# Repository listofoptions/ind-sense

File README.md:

# ind-sense
a prototype mechanical keyboard design based on inductive and capacitive sensing

project folder layout:
* cad        - contains the kicad and autocad files for pcb and switch design
* datasheets - information about the mechanical and electrical components used
* jupyter    - ipython notebook for the theory of operation 
* layout     - proposed eventual keyboard layouts
* scripts    - help scripts for use with design
* spice      - ltspice simulation source 

the main driving idea behind this keyboard switch design is to to build an even
more reliable beam spring like keyboard, that is a non conductivly sensed switch
with a high lifetime. the main mechanism of failure of most capacitive switches
is dirt and dust sensitivity, 
# ind-sense
a prototype mechanical keyboard design based on inductive and capacitive sensing

project folder layout:
* cad        - contains the kicad and autocad files for pcb and switch design
* datasheets - information about the mechanical and electrical components used
* jupyter    - ipython notebook for the theory of operation 
* layout     - proposed eventual keyboard layouts
* scripts    - help scripts for use with design
* spice      - ltspice simulation source 

the main driving idea behind this keyboard switch design is to to build an even
more reliable beam spring like keyboard, that is a non conductivly sensed switch
with a high lifetime. the main mechanism of failure of most capacitive switches
is dirt and dust sensitivity, which can be mitigated against by the use of a
spacer. This however makes the capacitive mechanism useless, (too much distance
at low voltages) to ensure the functionality of a such a mechanism I use an
inductive pad as the sensing element, such that when a peice of silicon steel
laminate is placed near the pad (with a protective spacer between!) the 
inductance, and hence the impedence of the circuit is changed. this of couse can
be sensed by the controller.

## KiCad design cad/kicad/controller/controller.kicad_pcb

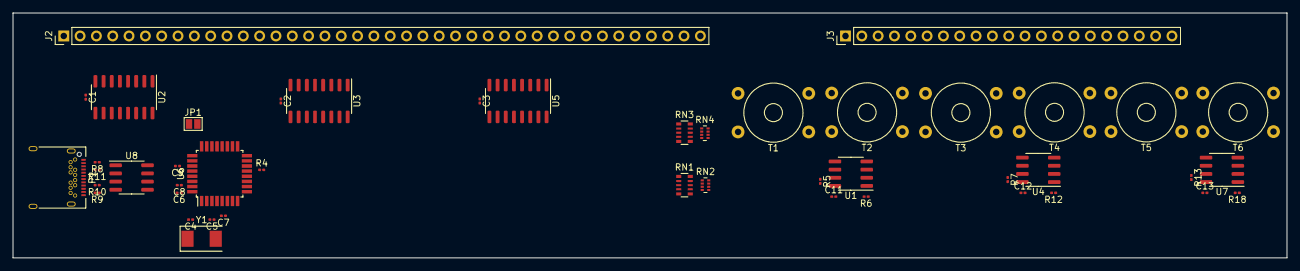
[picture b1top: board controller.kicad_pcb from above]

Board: 2 copper layers, 198.2 x 38.1 mm, 46 parts (0 on the bottom side), 86 nets, no tracks yet.

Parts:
C1, C2, C3, C6, C7, C8, C11, C12, C13: 0U1; C_0201_0603Metric
C4, C5: 22P; C_0201_0603Metric
C9: 1U; C_0201_0603Metric
J2: COLUMNS; PinHeader_1x40_P2.54mm_Vertical
J3: ROW; PinHeader_1x21_P2.54mm_Vertical
JP1: RESET; SolderJumper-2_P1.3mm_Open_Pad1.0x1.5mm
P1: USB_C_Plug_USB2.0; USB_C_Receptacle_Amphenol_12401548E4-2A
R4, R5, R6, R7, R12, R13, R18: 10K; R_0201_0603Metric
R8, R9: 5K1; R_0201_0603Metric
R10, R11: 22; R_0201_0603Metric
RN1, RN3: R_Pack05; R_Array_Convex_5x0603
RN2, RN4: R_Pack04; R_Array_Concave_4x0402
T1, T2, T3, T4, T5, T6: Transformer_1P_1S; Transformer_Toroid_Horizontal_D9.0mm_Amidon-T30
U1, U4, U7: LM393; SOIC-8_3.9x4.9mm_P1.27mm
U2, U3, U5: 74HC595; SOIC-16_3.9x9.9mm_P1.27mm
U6: ATmega32U2-AU; TQFP-32_7x7mm_P0.8mm
U8: USB6B1; SOIC-8_3.9x4.9mm_P1.27mm
Y1: 16M; Crystal_SMD_0603-2Pin_6.0x3.5mm

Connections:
+5V: C1.1, C2.1, C3.1, C6.1, C7.1, C8.1, C11.1, C12.1, C13.1, P1.A4, P1.A9, P1.B4, P1.B9, R5.2, R6.2, R7.2, R12.2, R13.2, R18.2, U1.8, U2.16, U3.16, U4.8, U5.16, U6.4, U6.31, U6.32, U7.8, U8.1, U8.8
/CLOCK: U2.11, U3.11, U5.11, U6.15
/COL1: J2.3, U2.7
/COL2: J2.5, U2.6
/COL3: J2.6, U2.5
/COL4: J2.8, U2.4
/COL5: J2.9, U2.3
/COL6: J2.11, U2.2
/COL7: J2.12, U2.1
/COL8: J2.14, U2.15
/COL9: J2.15, U3.7
/COL10: J2.17, U3.6
/COL11: J2.18, U3.5
/COL12: J2.20, U3.4
/COL13: J2.21, U3.3
/COL14: J2.23, U3.2
/COL15: J2.24, U3.1
/COL16: J2.26, U3.15
/COL17: J2.27, U5.7
/COL18: J2.29, U5.6
/COL19: J2.30, U5.5
/COL20: J2.32, U5.4
/COL21: J2.33, U5.3
/COL22: J2.35, U5.2
/COL23: J2.36, U5.1
/COL24: J2.38, U5.15
/CROWREF: RN1.10, RN2.8, U1.2, U1.6, U4.2, U4.6, U7.2, U7.6
/CROWREFDAC1: RN1.1, U6.26
/CROWREFDAC2: RN1.2, U6.25
/CROWREFDAC3: RN1.3, U6.23
/CROWREFDAC4: RN1.4, U6.22
/D+: U6.29, U8.7
/D-: U6.30, U8.6
/LE: U2.12, U3.12, U5.12, U6.18
/OUT1: R18.1, U6.11, U7.1
/OUT2: R13.1, U6.10, U7.7
/OUT3: R12.1, U4.1, U6.9
/OUT4: R7.1, U4.7, U6.8
/OUT5: R6.1, U1.1, U6.7
/OUT6: R5.1, U1.7, U6.6
/ROW1: T1.3, U1.5
/ROW1+: J3.3, T1.2
/ROW1-: J3.4, T1.1
/ROW2: T2.3, U1.3
/ROW2+: J3.6, T2.2
/ROW2-: J3.7, T2.1
/ROW3: T3.3, U4.5
/ROW3+: J3.9, T3.2
/ROW3-: J3.10, T3.1
/ROW4: T4.3, U4.3
/ROW4+: J3.12, T4.2
/ROW4-: J3.13, T4.1
/ROW5: T5.3, U7.5
/ROW5+: J3.15, T5.2
/ROW5-: J3.16, T5.1
/ROW6: T6.3, U7.3
/ROW6+: J3.18, T6.2
/ROW6-: J3.19, T6.1
/SDI: U2.14, U6.16
/STAGE1: U2.9, U3.14
/STAGE2: U3.9, U5.14
/TROWREF: RN3.10, RN4.8, T1.4, T2.4, T3.4, T4.4, T5.4, T6.4
/TROWREFDAC1: RN3.1, U6.19
/TROWREFDAC2: RN3.2, U6.20
/TROWREFDAC3: RN3.3, U6.21
/TROWREFDAC4: RN3.4, U6.5
/X+: C5.1, U6.2, Y1.2
/X-: C4.2, U6.1, Y1.1
/~OE: U2.13, U3.13, U5.13, U6.14
GND: C1.2, C2.2, C3.2, C4.1, C5.2, C6.2, C7.2, C8.2, C9.2, C11.2, C12.2, C13.2, JP1.1, P1.A1, P1.A12, P1.B1, P1.B12, P1.S1, R4.2, R8.1, R9.1, U1.4, U2.8, U2.10, U3.8, U3.10, U4.4, U5.8, U5.10, U6.3, U6.28, U7.4, U8.4, U8.5
GNDREF: J2.1, J2.2, J2.4, J2.7, J2.10, J2.13, J2.16, J2.19, J2.22, J2.25, J2.28, J2.31, J2.34, J2.37, J2.39, J2.40, J3.1, J3.2, J3.5, J3.8, J3.11, J3.14, J3.17, J3.20, J3.21, RN1.5, RN3.5
unnamed: C9.1, U6.27
unnamed: JP1.2, U6.24
unnamed: P1.A5, R8.2
unnamed: P1.A6, R11.2
unnamed: P1.A7, R10.2
unnamed: P1.B5, R9.2
unnamed: R4.1, U6.13
unnamed: R10.1, U8.3
unnamed: R11.1, U8.2
unnamed: RN1.6, RN1.7, RN2.3
unnamed: RN1.8, RN2.6, RN2.7
unnamed: RN1.9, RN2.1
unnamed: RN3.6, RN3.7, RN4.3
unnamed: RN3.8, RN4.6, RN4.7
unnamed: RN3.9, RN4.1

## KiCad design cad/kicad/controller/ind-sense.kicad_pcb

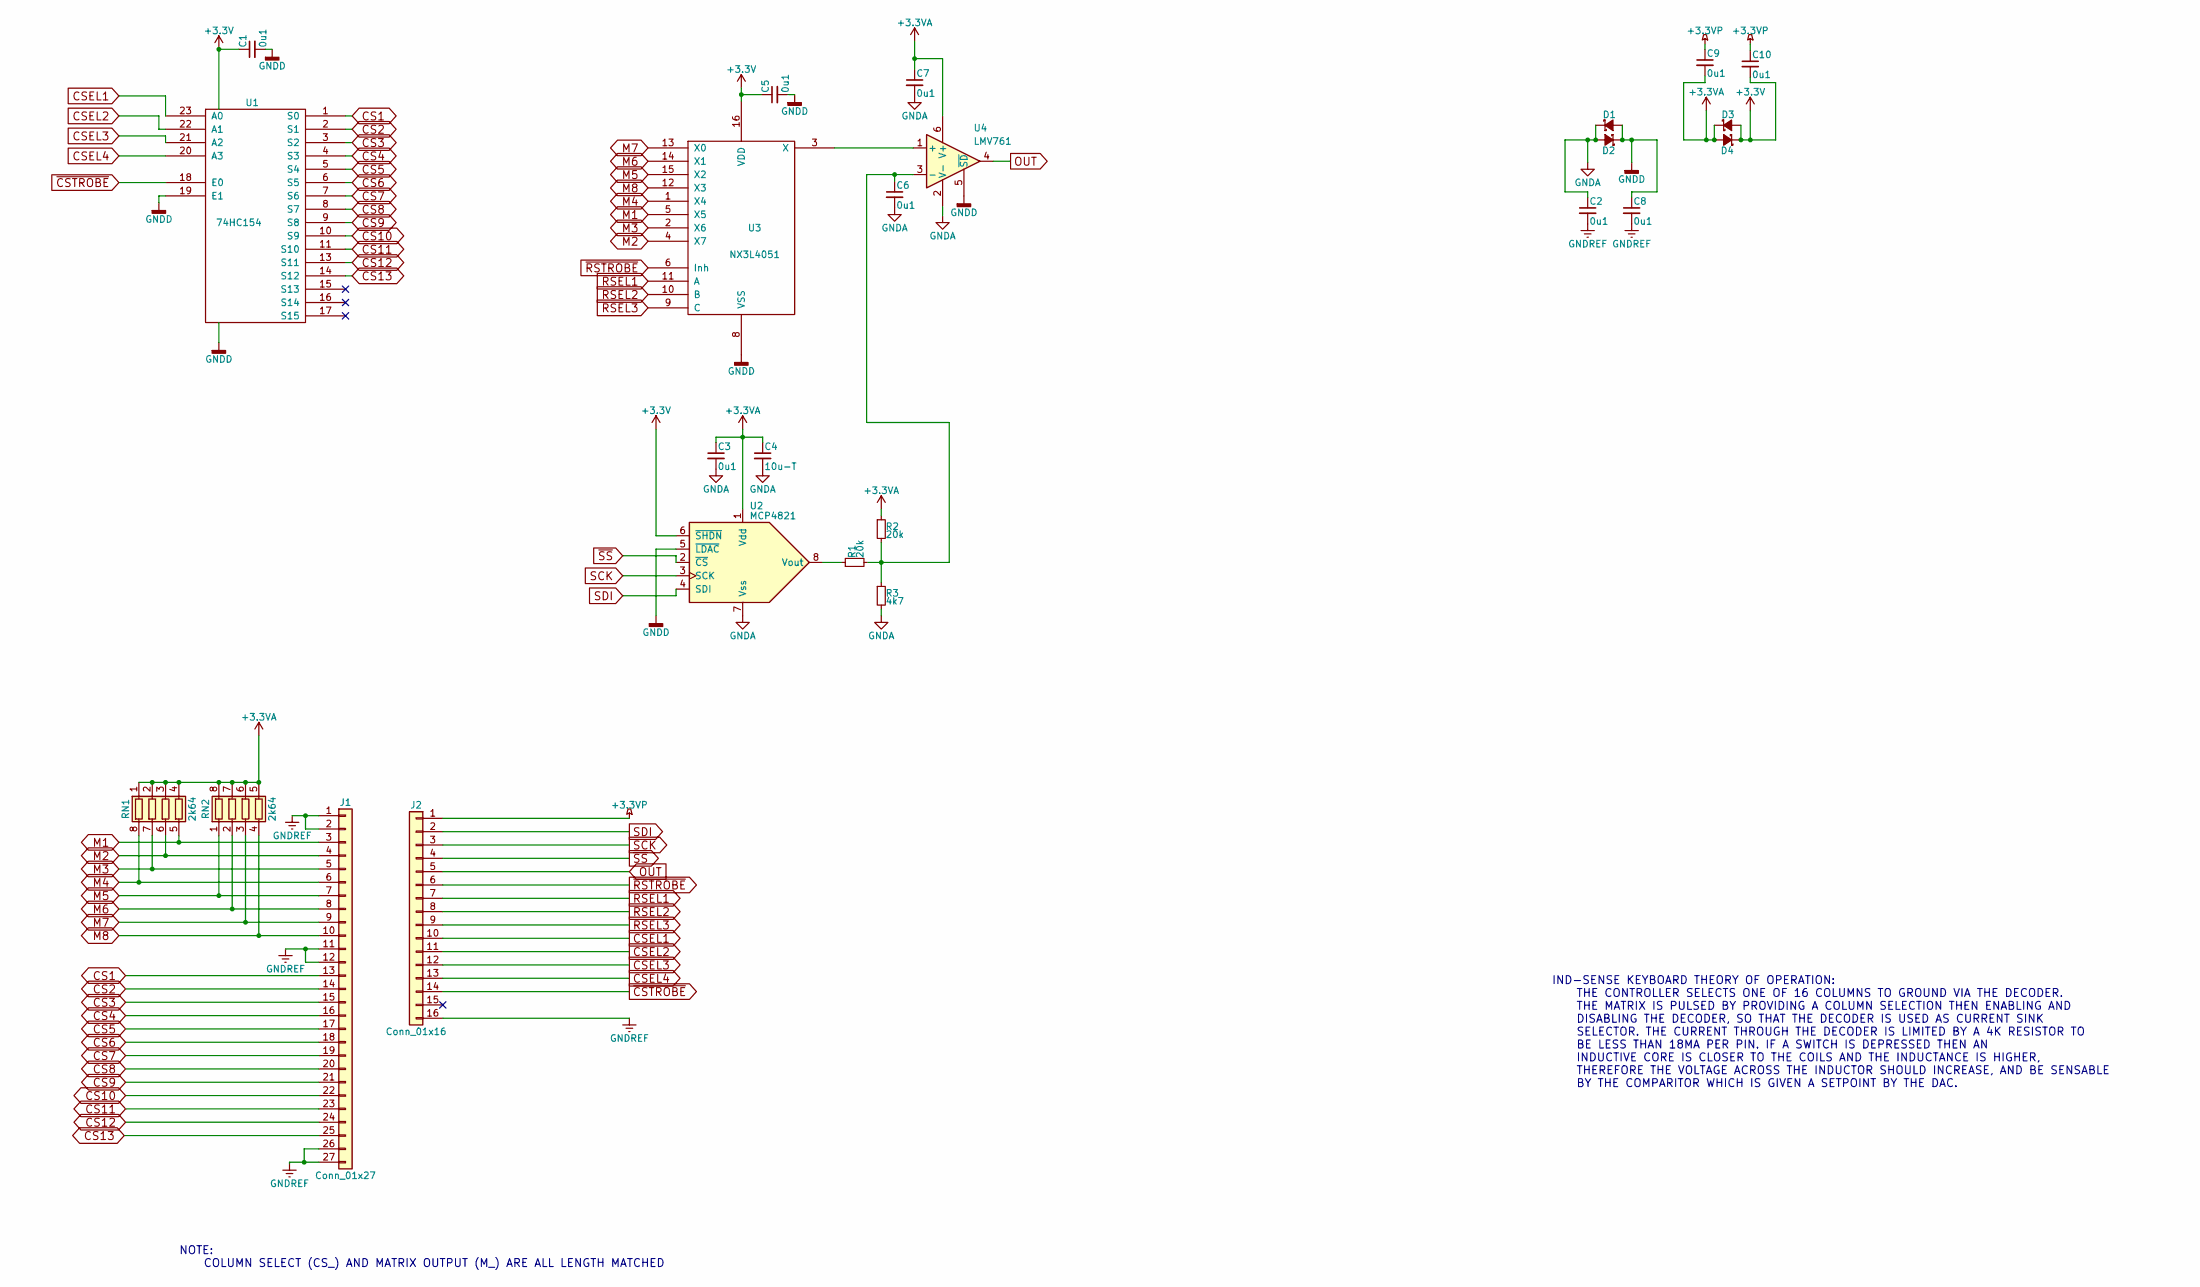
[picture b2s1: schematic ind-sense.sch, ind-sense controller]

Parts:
C1, C2, C3, C5, C6, C7, C8, C9, C10: 0u1; C_0603_HandSoldering
C4: 10u-T; CP_Tantalum_Case-R_EIA-2012-12_Hand
D1, D2, D3, D4: D_0603
J1: Conn_01x27; Pin_Header_Straight_1x27_Pitch2.54mm
J2: Conn_01x16; Pin_Header_Straight_1x16_Pitch2.54mm
R1, R2: 20k; R_0603_HandSoldering
R3: 4k7; R_0603_HandSoldering
RN1, RN2: 2k64; R_Array_Convex_4x0603
U1: 74HC154; TSSOP-24_4.4x7.8mm_Pitch0.65mm
U2: MCP4821; MSOP-8_3x3mm_Pitch0.65mm
U3: NX3L4051; TSSOP-16_4.4x5mm_Pitch0.65mm
U4: LMV761; SOT-23-6_Handsoldering

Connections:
+3.3VA: C3.1, C4.1, C7.1, C9.2, D3.1 (K), D4.2 (A), R2.1, RN1.1 (R1.1), RN1.2 (R2.1), RN1.3 (R3.1), RN1.4 (R4.1), RN2.5 (R4.2), RN2.6 (R3.2), RN2.7 (R2.2), RN2.8 (R1.2), U2.1 (Vdd), U4.6 (V+)
+3.3VP: C9.1, C10.1, J2.1
+3V3: C1.1, C5.1, C10.2, D3.2 (A), D4.1 (K), U1.24 (VCC), U2.6 (~SHDN), U3.16 (VDD)
CS1: J1.13, U1.1 (S0)
CS2: J1.14, U1.2 (S1)
CS3: J1.15, U1.3 (S2)
CS4: J1.16, U1.4 (S3)
CS5: J1.17, U1.5 (S4)
CS6: J1.18, U1.6 (S5)
CS7: J1.19, U1.7 (S6)
CS8: J1.20, U1.8 (S7)
CS9: J1.21, U1.9 (S8)
CS10: J1.22, U1.10 (S9)
CS11: J1.23, U1.11 (S10)
CS12: J1.24, U1.13 (S11)
CS13: J1.25, U1.14 (S12)
CSEL1: J2.10, U1.23 (A0)
CSEL2: J2.11, U1.22 (A1)
CSEL3: J2.12, U1.21 (A2)
CSEL4: J2.13, U1.20 (A3)
GND: C1.2, C5.2, C8.1, D1.2 (A), D2.1 (K), U1.12 (GND), U1.19 (E1), U2.5 (~LDAC), U3.8 (VSS), U4.5 (~SD)
GNDA: C2.1, C3.2, C4.2, C6.2, C7.2, D1.1 (K), D2.2 (A), R3.2, U2.7 (Vss), U4.2 (V-)
GNDREF: C2.2, C8.2, J1.1, J1.2, J1.11, J1.12, J1.26, J1.27, J2.16
M1: J1.3, RN1.5 (R4.2), U3.5 (X5)
M2: J1.4, RN1.6 (R3.2), U3.4 (X7)
M3: J1.5, RN1.7 (R2.2), U3.2 (X6)
M4: J1.6, RN1.8 (R1.2), U3.1 (X4)
M5: J1.7, RN2.1 (R1.1), U3.15 (X2)
M6: J1.8, RN2.2 (R2.1), U3.14 (X1)
M7: J1.9, RN2.3 (R3.1), U3.13 (X0)
M8: J1.10, RN2.4 (R4.1), U3.12 (X3)
unnamed: C6.1, R1.2, R2.2, R3.1, U4.3 (-)
unnamed: R1.1, U2.8 (Vout)
unnamed: U3.3 (X), U4.1 (+)
OUT: J2.5, U4.4
RSEL1: J2.7, U3.11 (A)
RSEL2: J2.8, U3.10 (B)
RSEL3: J2.9, U3.9 (C)
SCK: J2.3, U2.3 (SCK)
SDI: J2.2, U2.4 (SDI)
~CSTROBE: J2.14, U1.18 (E0)
~RSTROBE: J2.6, U3.6 (Inh)
~SS: J2.4, U2.2 (~CS)

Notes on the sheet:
IND-SENSE KEYBOARD THEORY OF OPERATION: THE CONTROLLER SELECTS ONE OF 16 COLUMNS TO GROUND VIA THE DECODER. THE MATRIX IS PULSED BY PROVIDING A COLUMN SELECTION THEN ENABLING AND DISABLING THE DECODER, SO THAT THE DECODER IS USED AS CURRENT SINK SELECTOR. THE CURRENT THROUGH THE DECODER IS LIMITED 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
NOTE: COLUMN SELECT (CS_) AND MATRIX OUTPUT (M_) ARE ALL LENGTH MATCHED

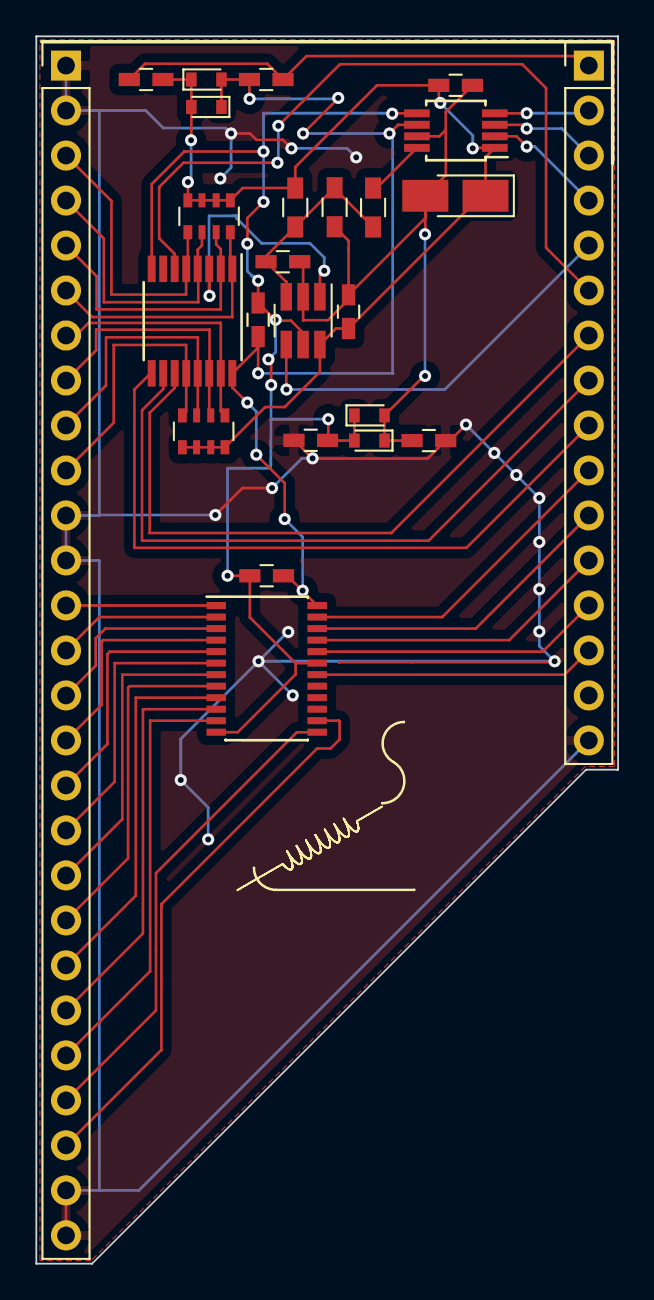
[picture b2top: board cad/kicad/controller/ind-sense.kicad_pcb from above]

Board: 2 copper layers, 32.8 x 69.3 mm, 25 parts (0 on the bottom side), 43 nets.

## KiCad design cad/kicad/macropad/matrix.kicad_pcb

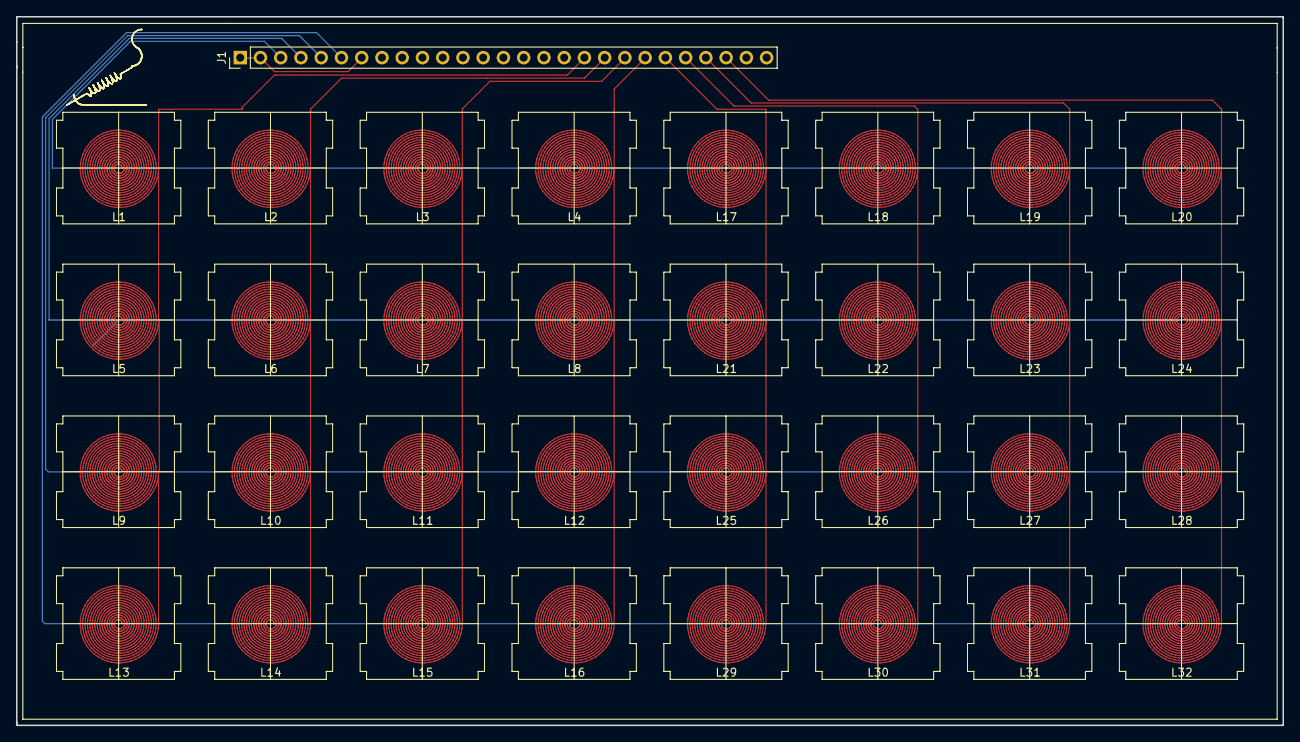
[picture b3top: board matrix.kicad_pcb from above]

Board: 2 copper layers, 158.9 x 88.9 mm, 33 parts (0 on the bottom side), 13 nets.

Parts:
J1: Conn_01x27; Pin_Header_Straight_1x27_Pitch2.54mm
L1, L2, L3, L4, L5, L6, L7, L8, L9, L10, L11, L12, L13, L14, L15, L16, L17, L18, L19, L20, L21, L22, L23, L24, L25, L26, L27, L28, L29, L30, L31, L32: pad

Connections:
/MCN10: J1.6, L13.2, L14.2, L15.2, L16.2, L29.2, L30.2, L31.2, L32.2
/MCN11: J1.5, L9.2, L10.2, L11.2, L12.2, L25.2, L26.2, L27.2, L28.2
/MCN12: J1.4, L5.2, L6.2, L7.2, L8.2, L21.2, L22.2, L23.2, L24.2
/MCN13: J1.3, L1.2, L2.2, L3.2, L4.2, L17.2, L18.2, L19.2, L20.2
/MRP1: J1.18, L1.1, L5.1, L9.1, L13.1
/MRP2: J1.19, L2.1, L6.1, L10.1, L14.1
/MRP3: J1.20, L3.1, L7.1, L11.1, L15.1
/MRP4: J1.21, L4.1, L8.1, L12.1, L16.1
/MRP5: J1.22, L17.1, L21.1, L25.1, L29.1
/MRP6: J1.23, L18.1, L22.1, L26.1, L30.1
/MRP7: J1.24, L19.1, L23.1, L27.1, L31.1
/MRP8: J1.25, L20.1, L24.1, L28.1, L32.1
GNDREF: J1.1, J1.2, J1.7, J1.8, J1.9, J1.10, J1.11, J1.12, J1.13, J1.14, J1.15, J1.16, J1.17, J1.26, J1.27

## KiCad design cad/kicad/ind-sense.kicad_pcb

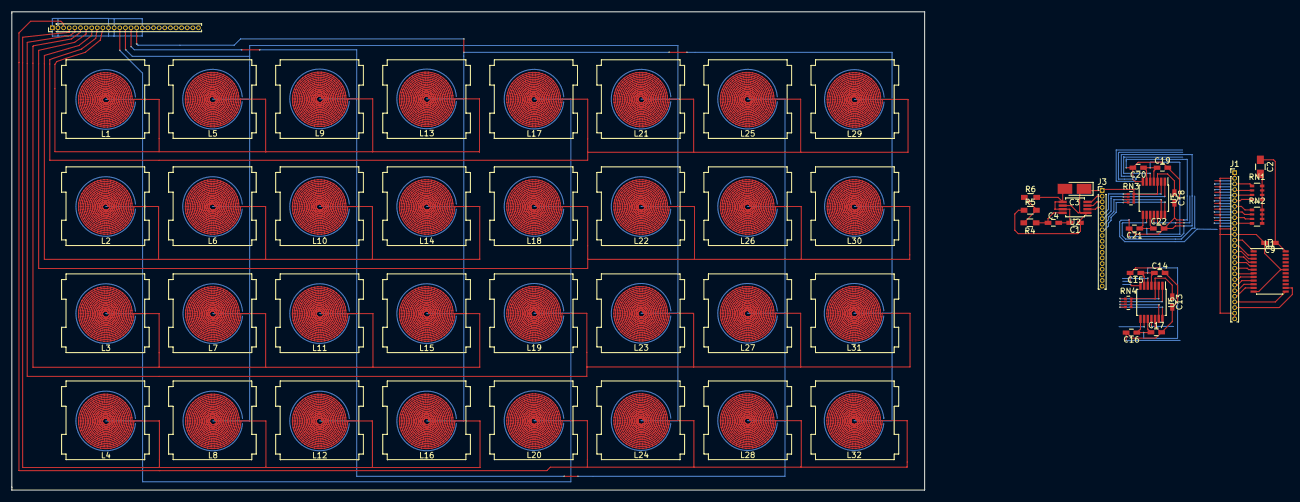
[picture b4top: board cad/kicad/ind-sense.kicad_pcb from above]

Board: 2 copper layers, 162.4 x 85.1 mm, 61 parts (0 on the bottom side), 55 nets.

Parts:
C1, C13, C14, C15, C16, C17, C18, C19, C20, C21, C22: 0u1; C_0603_HandSoldering
C2: 100u; C_0805_HandSoldering
C3: 10u-T; CP_Tantalum_Case-R_EIA-2012-12_Hand
C4, C9: 1u; C_0603_HandSoldering
J1, J2: Conn_01x27; Pin_Header_Straight_1x27_Pitch1.00mm
J3: Conn_01x18; Pin_Header_Straight_1x18_Pitch1.00mm
L1, L2, L3, L4, L5, L6, L7, L8, L9, L10, L11, L12, L13, L14, L15, L16, L17, L18, L19, L20, L21, L22, L23, L24, L25, L26, L27, L28, L29, L30, L31, L32: pad
R4, R5: 20k; R_0603_HandSoldering
R6: 4k7; R_0603_HandSoldering
RN1, RN2: 330; R_Array_Convex_4x0603
RN3, RN4: 66k; R_Array_Convex_4x0402
U1: 74HC154; TSSOP-24_4.4x7.8mm_Pitch0.65mm
U2: MCP4821; MSOP-8_3x3mm_Pitch0.65mm
U5, U6: CMP04; TSSOP-14_4.4x5mm_Pitch0.65mm

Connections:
+3V3: C1.1, C2.1, C3.1, C9.1, C13.1, C18.1, J3.1, R5.1, RN3.5, RN3.6, RN3.7, RN3.8, RN4.5, RN4.6, RN4.7, RN4.8, U1.24, U2.1, U2.6, U5.3, U6.3
/matrix/MCN1: J2.13, L1.2, L2.2, L3.2, L4.2, L17.2, L18.2, L19.2, L20.2
/matrix/MCN2: J2.14, L5.2, L6.2, L7.2, L8.2, L21.2, L22.2, L23.2, L24.2
/matrix/MCN3: J2.15, L9.2, L10.2, L11.2, L12.2, L25.2, L26.2, L27.2, L28.2
/matrix/MCN4: J2.16, L13.2, L14.2, L15.2, L16.2, L29.2, L30.2, L31.2, L32.2
/matrix/MRP1: J2.10, L1.1, L5.1, L9.1, L13.1
/matrix/MRP2: J2.8, L2.1, L6.1, L10.1, L14.1
/matrix/MRP3: J2.6, L3.1, L7.1, L11.1, L15.1
/matrix/MRP4: J2.4, L4.1, L8.1, L12.1, L16.1
/matrix/MRP5: J2.9, L17.1, L21.1, L25.1, L29.1
/matrix/MRP6: J2.7, L18.1, L22.1, L26.1, L30.1
/matrix/MRP7: J2.5, L19.1, L23.1, L27.1, L31.1
/matrix/MRP8: J2.3, L20.1, L24.1, L28.1, L32.1
CS1: J1.13, U1.1
CS2: J1.14, U1.2
CS3: J1.15, U1.3
CS4: J1.16, U1.4
CS5: J1.17, U1.5
CS6: J1.18, U1.6
CS7: J1.19, U1.7
CS8: J1.20, U1.8
CS9: J1.21, U1.9
CS10: J1.22, U1.10
CS11: J1.23, U1.11
CS12: J1.24, U1.13
CS13: J1.25, U1.14
GND: C1.2, C3.2, C4.2, C9.2, C13.2, C14.2, C15.2, C16.2, C17.2, C18.2, C19.2, C20.2, C21.2, C22.2, J1.1, J1.2, J1.11, J1.12, J1.26, J1.27, J3.18, R6.2, U1.12, U1.19, U2.5, U2.7, U5.12, U6.12
GNDREF: J2.1, J2.2, J2.11, J2.12, J2.17, J2.18, J2.19, J2.20, J2.21, J2.22, J2.23, J2.24, J2.25, J2.26, J2.27, L1.3, L2.3, L3.3, L4.3, L5.3, L6.3, L7.3, L8.3, L9.3, L10.3, L11.3, L12.3, L13.3, L14.3, L15.3, L16.3, L17.3, L18.3, L19.3, L20.3, L21.3, L22.3, L23.3, L24.3, L25.3, L26.3, L27.3, L28.3, L29.3, L30.3, L31.3, L32.3
M1: J1.3, RN1.1, U5.5
M2: J1.4, RN1.2, U5.7
M3: J1.5, RN1.3, U5.11
M4: J1.6, RN1.4, U5.9
M5: J1.7, RN2.1, U6.5
M6: J1.8, RN2.2, U6.7
M7: J1.9, RN2.3, U6.11
M8: J1.10, RN2.4, U6.9
unnamed: C2.2, RN1.5, RN1.6, RN1.7, RN1.8, RN2.5, RN2.6, RN2.7, RN2.8
unnamed: C4.1, R4.1, U2.8
S1: J3.5, RN3.1, U5.2
S2: J3.6, RN3.2, U5.1
S3: J3.7, RN3.3, U5.13
S4: J3.8, RN3.4, U5.14
S5: J3.9, RN4.1, U6.2
S6: J3.10, RN4.2, U6.1
S7: J3.11, RN4.3, U6.13
S8: J3.12, RN4.4, U6.14
SCK: J3.3, U2.3
SDI: J3.2, U2.4
SEL1: J3.13, U1.23
SEL2: J3.14, U1.22
SEL3: J3.15, U1.21
SEL4: J3.16, U1.20
SP: C14.1, C15.1, C16.1, C17.1, C19.1, C20.1, C21.1, C22.1, R4.2, R5.2, R6.1, U5.4, U5.6, U5.8, U5.10, U6.4, U6.6, U6.8, U6.10
~SS: J3.4, U2.2
~STROBE: J3.17, U1.18

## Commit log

2018-05-30 updaded board and added some further documentation for egineering desicions, need to add further documentation to help people get up to speed with the project
2018-06-01 added logo, and started work on panelizing the demo pcb
2018-06-01 added TODO
2018-06-03 seperated the controller from the demo macropad, remade the controller to hopefully be less succeptable to emi, and digital interferance.
2018-06-04 removed some unneeded files
2018-06-09 updated controller with a lower part count equivalent, that should also be more accurate. need to have an actuall EE review the board and it's design
2018-06-10 worked on theory of operation spice, need to find a reliable equivalent circuit model, and a physical example of the pad
2020-03-07 in process redesign based on ADI/keytech induction board
